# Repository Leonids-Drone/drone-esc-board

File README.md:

# Electric speed control board

Single channel ESC designed for Leonids drone, compatible with AM32 firmware.

## Current stage: Demo board

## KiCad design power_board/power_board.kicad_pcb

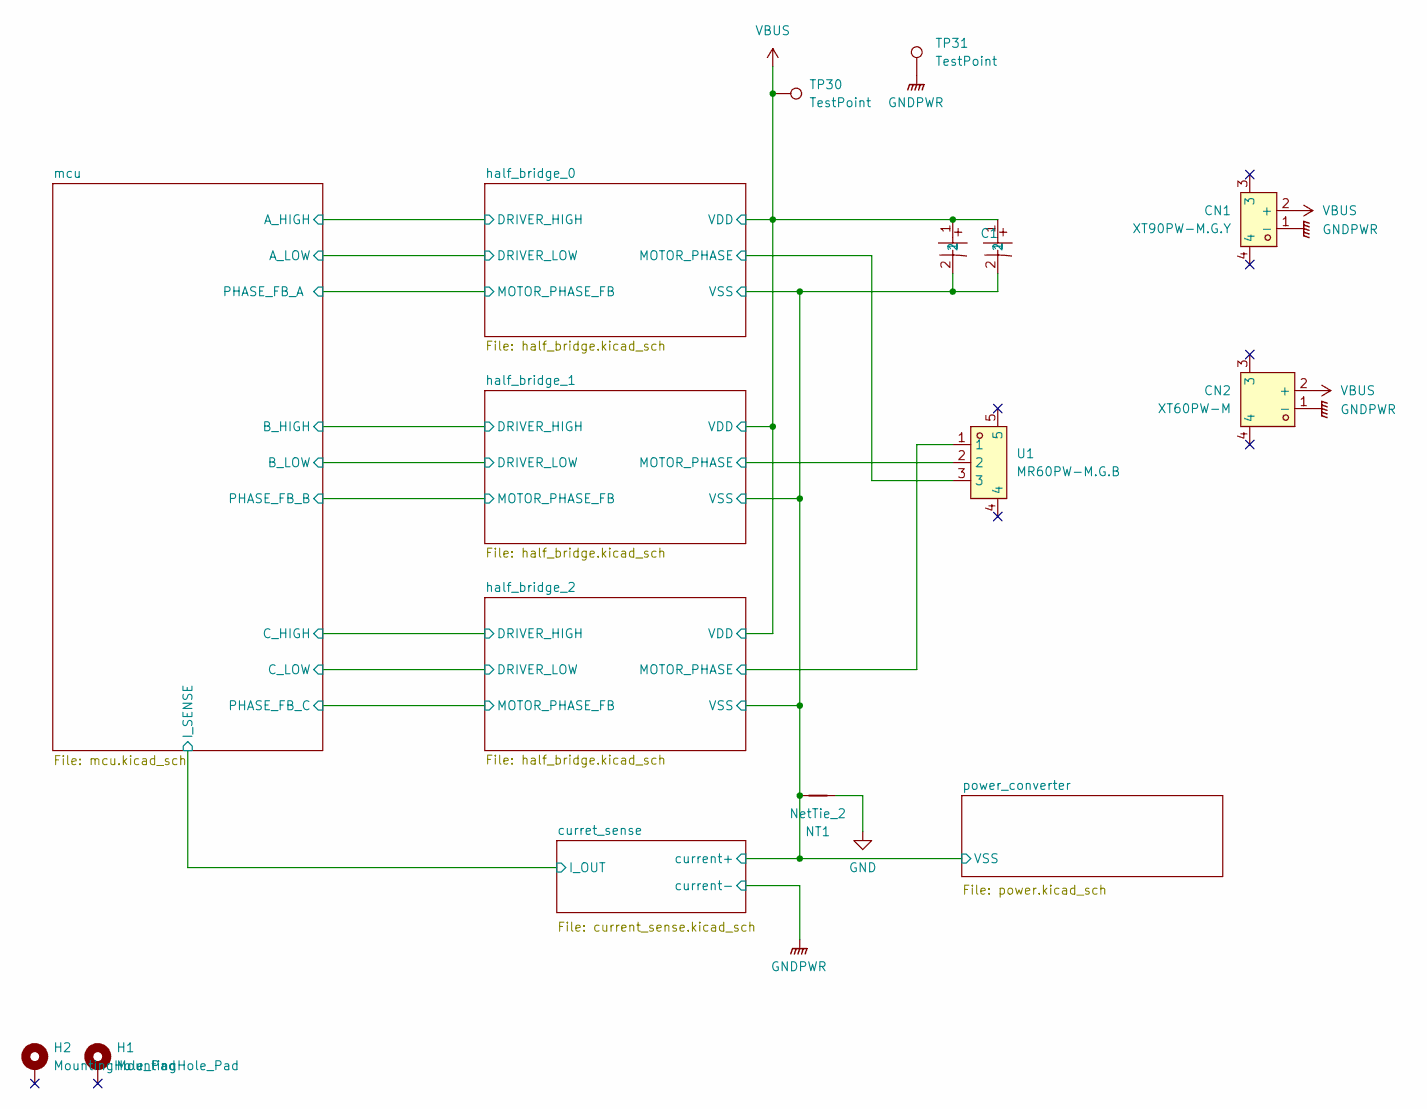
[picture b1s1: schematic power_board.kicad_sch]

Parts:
C1, C2: ERS1KM101G16OT; CAP-TH_BD10.0-P5.00-D1.0-FD; LCSC Part C106679
CN1: XT90PW-M.G.Y; CONN-TH_XT90PW-M.G.Y; LCSC Part C3040689
CN2: XT60PW-M; CONN-TH_XT60PW-M; LCSC Part C98732
H1, H2: MountingHole_Pad; MountingHole_4.3mm_M4_Pad_Via
NT1: NetTie_2; NetTie-2_THT_Pad0.3mm
TP30, TP31: TestPoint; SMD_RH-5015
U1: MR60PW-M.G.B; CONN-TH_MR60PW; LCSC Part C19268044

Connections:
/curret_sense/current+: C1.2, C2.2, NT1.2; also elsewhere on the board
/half_bridge_0/MOTOR_PHASE: U1.3; also elsewhere on the board
/half_bridge_1/MOTOR_PHASE: U1.2; also elsewhere on the board
/half_bridge_2/MOTOR_PHASE: U1.1; also elsewhere on the board
GND: NT1.1; also elsewhere on the board
GNDPWR: CN1.1 (-), CN2.1 (-), TP31.1; also elsewhere on the board
VBUS: C1.1, C2.1, CN1.2 (+), CN2.2 (+), TP30.1; also elsewhere on the board

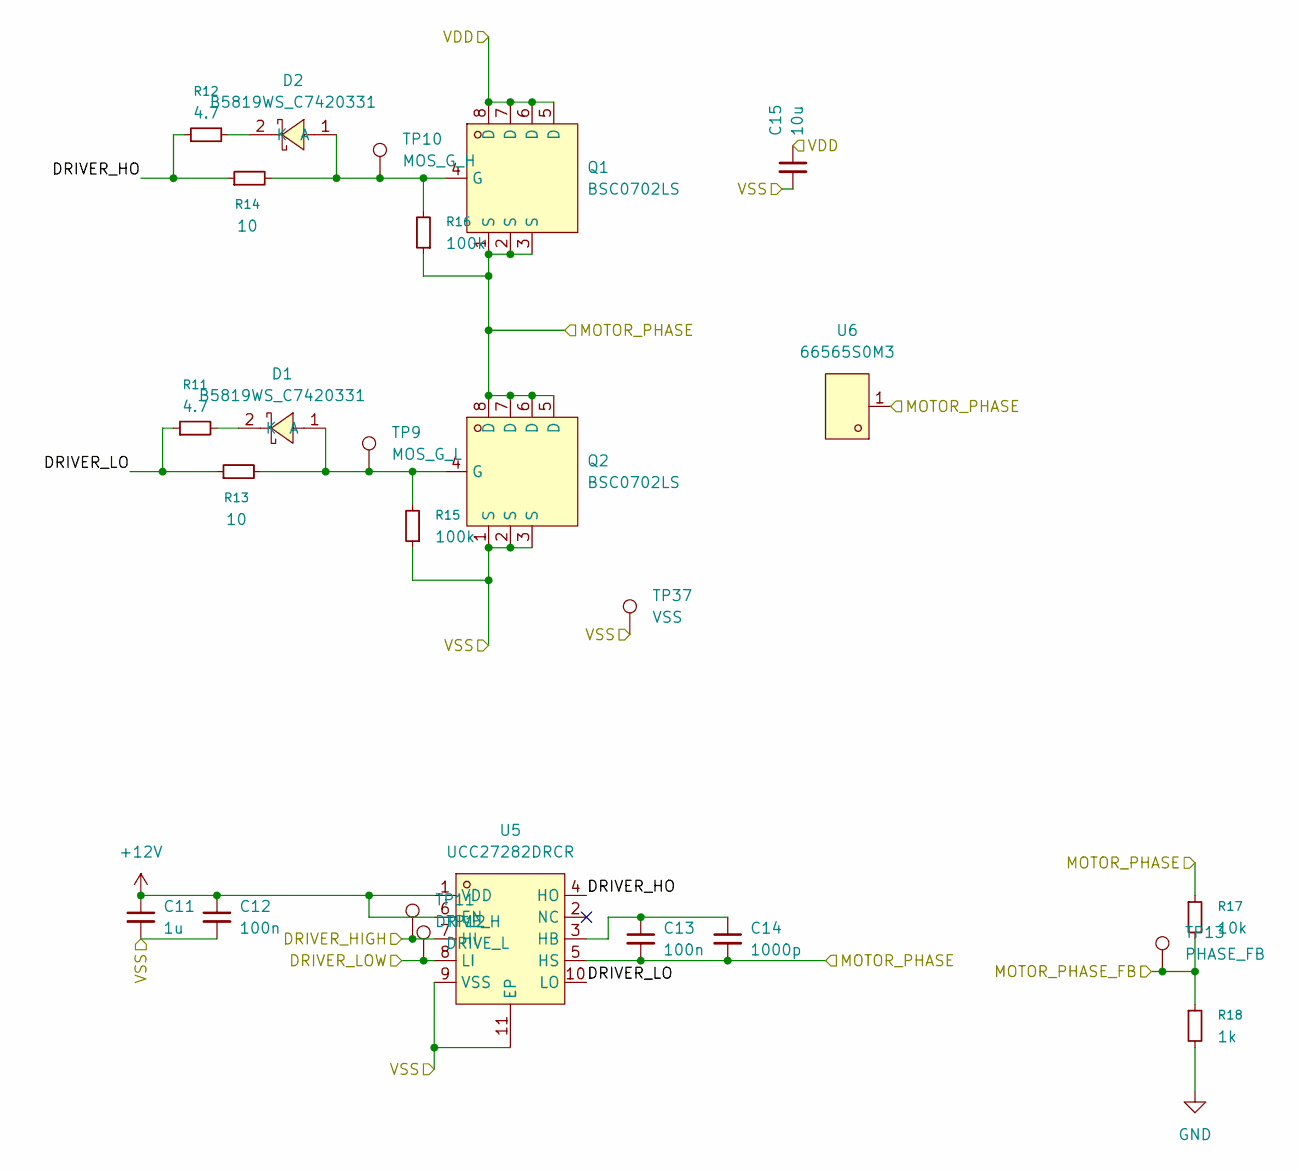
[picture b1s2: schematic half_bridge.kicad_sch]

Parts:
C11: 1u; C_0603_1608Metric
C12, C13: 100n; C_0603_1608Metric
C14: 1000p; C_0603_1608Metric
C15: 10u; C_1210_3225Metric
D1, D2: B5819WS_C7420331; SOD-323_L1.7-W1.3-LS2.5-FD; LCSC Part C7420331
Q1, Q2: BSC0702LS; PG-TDSON-8_L5.0-W6.0-P1.27-BL-EP; LCSC Part C501503
R11, R12: 4.7; R_0603_1608Metric
R13, R14: 10; R_0603_1608Metric
R15, R16: 100k; R_0603_1608Metric
R17: 10k; R_0603_1608Metric
R18: 1k; R_0603_1608Metric
TP9: MOS_G_L; SMD_RH-5015
TP10: MOS_G_H; SMD_RH-5015
TP11: DRIVE_H; SMD_RH-5015
TP12: DRIVE_L; SMD_RH-5015
TP13: PHASE_FB; SMD_RH-5015
TP37: VSS; SMD_RH-5015
U5: UCC27282DRCR; VSON-10_L3.0-W3.0-P0.50-TL-EP; LCSC Part C2677035
U6: 66565S0M3; CONN-SMD_66565S0M3; LCSC Part C41416690

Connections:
+12V: C11.1, C12.1, U5.1 (VDD), U5.6 (EN); also elsewhere on the board
/curret_sense/current+: C11.2, C12.2, C15.2, Q2.1 (S), Q2.2 (S), Q2.3 (S), R15.1, TP37.1, U5.9 (VSS), U5.11 (EP); also elsewhere on the board
/half_bridge_0/DRIVER_HIGH: TP11.1, U5.7 (HI); also elsewhere on the board
/half_bridge_0/DRIVER_HO: R12.1, R14.1, U5.4 (HO)
/half_bridge_0/DRIVER_LO: R11.1, R13.1, U5.10 (LO)
/half_bridge_0/DRIVER_LOW: TP12.1, U5.8 (LI); also elsewhere on the board
/half_bridge_0/MOTOR_PHASE: C13.2, C14.2, Q1.1 (S), Q1.2 (S), Q1.3 (S), Q2.5 (D), Q2.6 (D), Q2.7 (D), Q2.8 (D), R16.1, R17.1, U5.5 (HS), U6.1; also elsewhere on the board
/half_bridge_0/MOTOR_PHASE_FB: R17.2, R18.1, TP13.1; also elsewhere on the board
GND: R18.2; also elsewhere on the board
unnamed: D1.1 (A), Q2.4 (G), R13.2, R15.2, TP9.1
unnamed: D1.2 (K), R11.2
unnamed: D2.1 (A), Q1.4 (G), R14.2, R16.2, TP10.1
unnamed: D2.2 (K), R12.2
unnamed: C13.1, C14.1, U5.3 (HB)
VBUS: C15.1, Q1.5 (D), Q1.6 (D), Q1.7 (D), Q1.8 (D); also elsewhere on the board

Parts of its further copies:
C16, C21: 1u; C_0603_1608Metric
C17, C18, C22, C23: 100n; C_0603_1608Metric
C19, C24: 1000p; C_0603_1608Metric
C20, C25: 10u; C_1210_3225Metric
D3, D4, D5, D6: B5819WS_C7420331; SOD-323_L1.7-W1.3-LS2.5-FD; LCSC Part C7420331
Q3, Q4, Q5, Q6: BSC0702LS; PG-TDSON-8_L5.0-W6.0-P1.27-BL-EP; LCSC Part C501503
R19, R20, R27, R28: 4.7; R_0603_1608Metric
R21, R22, R29, R30: 10; R_0603_1608Metric
R23, R24, R31, R32: 100k; R_0603_1608Metric
R25, R33: 10k; R_0603_1608Metric
R26, R34: 1k; R_0603_1608Metric
TP14, TP19: MOS_G_L; SMD_RH-5015
TP15, TP20: MOS_G_H; SMD_RH-5015
TP16, TP21: DRIVE_H; SMD_RH-5015
TP17, TP22: DRIVE_L; SMD_RH-5015
TP18, TP23: PHASE_FB; SMD_RH-5015
TP38, TP39: VSS; SMD_RH-5015
U7, U9: UCC27282DRCR; VSON-10_L3.0-W3.0-P0.50-TL-EP; LCSC Part C2677035
U8, U10: 66565S0M3; CONN-SMD_66565S0M3; LCSC Part C41416690

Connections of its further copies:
+12V: C16.1, C17.1, C21.1, C22.1, U7.1 (VDD), U7.6 (EN), U9.1 (VDD), U9.6 (EN); also elsewhere on the board
/curret_sense/current+: C16.2, C17.2, C20.2, C21.2, C22.2, C25.2, Q4.1 (S), Q4.2 (S), Q4.3 (S), Q6.1 (S), Q6.2 (S), Q6.3 (S), R23.1, R31.1, TP38.1, TP39.1, U7.9 (VSS), U7.11 (EP), U9.9 (VSS), U9.11 (EP); also elsewhere on the board
/half_bridge_1/DRIVER_HIGH: TP16.1, U7.7 (HI); also elsewhere on the board
/half_bridge_1/DRIVER_HO: R20.1, R22.1, U7.4 (HO)
/half_bridge_1/DRIVER_LO: R19.1, R21.1, U7.10 (LO)
/half_bridge_1/DRIVER_LOW: TP17.1, U7.8 (LI); also elsewhere on the board
/half_bridge_1/MOTOR_PHASE: C18.2, C19.2, Q3.1 (S), Q3.2 (S), Q3.3 (S), Q4.5 (D), Q4.6 (D), Q4.7 (D), Q4.8 (D), R24.1, R25.1, U7.5 (HS), U8.1; also elsewhere on the board
/half_bridge_1/MOTOR_PHASE_FB: R25.2, R26.1, TP18.1; also elsewhere on the board
/half_bridge_2/DRIVER_HIGH: TP21.1, U9.7 (HI); also elsewhere on the board
/half_bridge_2/DRIVER_HO: R28.1, R30.1, U9.4 (HO)
/half_bridge_2/DRIVER_LO: R27.1, R29.1, U9.10 (LO)
/half_bridge_2/DRIVER_LOW: TP22.1, U9.8 (LI); also elsewhere on the board
/half_bridge_2/MOTOR_PHASE: C23.2, C24.2, Q5.1 (S), Q5.2 (S), Q5.3 (S), Q6.5 (D), Q6.6 (D), Q6.7 (D), Q6.8 (D), R32.1, R33.1, U9.5 (HS), U10.1; also elsewhere on the board
/half_bridge_2/MOTOR_PHASE_FB: R33.2, R34.1, TP23.1; also elsewhere on the board
GND: R26.2, R34.2; also elsewhere on the board
unnamed: D3.1 (A), Q4.4 (G), R21.2, R23.2, TP14.1
unnamed: D3.2 (K), R19.2
unnamed: D4.1 (A), Q3.4 (G), R22.2, R24.2, TP15.1
unnamed: D4.2 (K), R20.2
unnamed: D5.1 (A), Q6.4 (G), R29.2, R31.2, TP19.1
unnamed: D5.2 (K), R27.2
unnamed: D6.1 (A), Q5.4 (G), R30.2, R32.2, TP20.1
unnamed: D6.2 (K), R28.2
unnamed: C18.1, C19.1, U7.3 (HB)
unnamed: C23.1, C24.1, U9.3 (HB)
VBUS: C20.1, C25.1, Q3.5 (D), Q3.6 (D), Q3.7 (D), Q3.8 (D), Q5.5 (D), Q5.6 (D), Q5.7 (D), Q5.8 (D); also elsewhere on the board

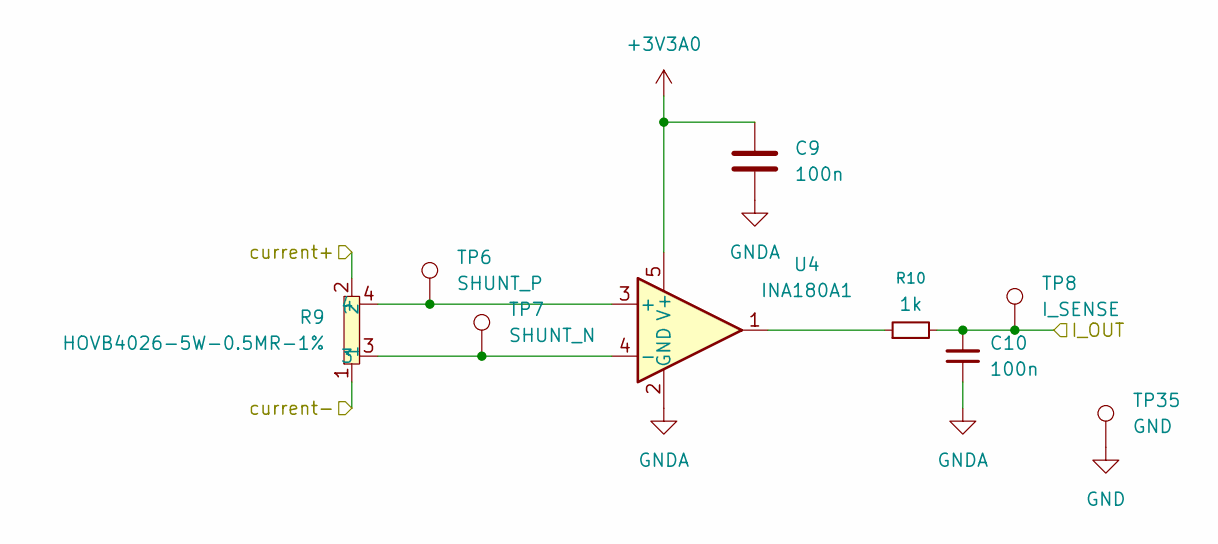
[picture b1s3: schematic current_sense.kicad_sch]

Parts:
C9, C10: 100n; C_0603_1608Metric
R9: HOVB4026-5W-0.5MR-1%; RES-SMD_4P-L10.8-W6.7; LCSC Part C481533
R10: 1k; R_0603_1608Metric
TP6: SHUNT_P; SMD_RH-5015
TP7: SHUNT_N; SMD_RH-5015
TP8: I_SENSE; SMD_RH-5015
TP35: GND; SMD_RH-5015
U4: INA180A1; SOT-23-5

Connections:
+3V3A0: C9.1, U4.5 (V+); also elsewhere on the board
/curret_sense/I_OUT: C10.2, R10.2, TP8.1; also elsewhere on the board
/curret_sense/current+: R9.2; also elsewhere on the board
GND: C9.2, C10.1, TP35.1, U4.2 (GND); also elsewhere on the board
GNDPWR: R9.1; also elsewhere on the board
unnamed: R10.1, U4.1
unnamed: R9.4, TP6.1, U4.3 (+)
unnamed: R9.3, TP7.1, U4.4 (-)

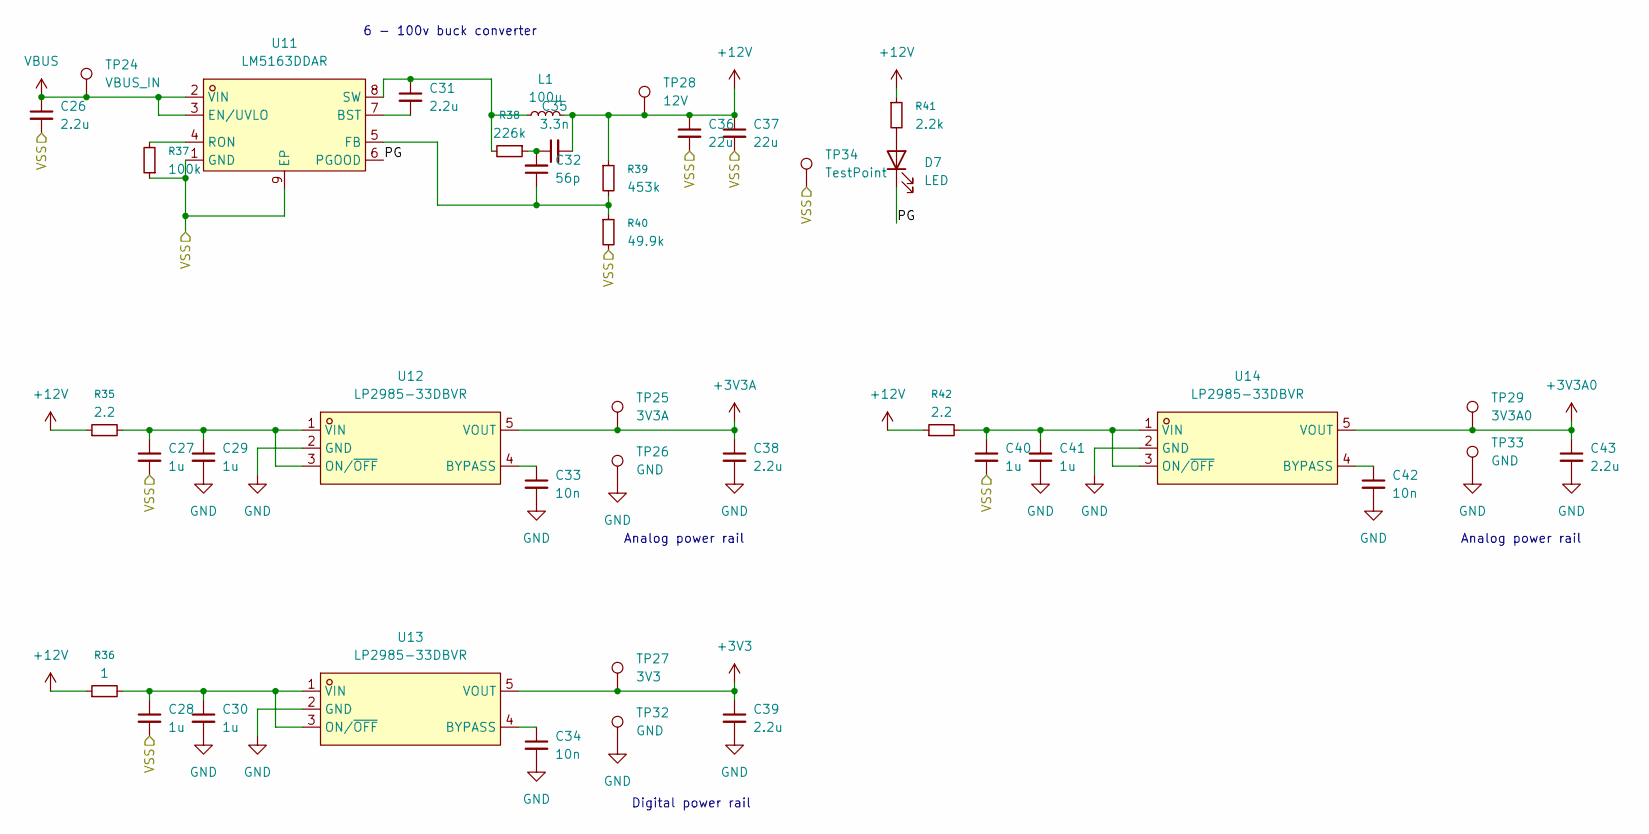
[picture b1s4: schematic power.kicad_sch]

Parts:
C26, C31, C38, C39, C43: 2.2u; C_0603_1608Metric
C27, C28, C29, C30, C40, C41: 1u; C_0603_1608Metric
C32: 56p; C_0603_1608Metric
C33, C34, C42: 10n; C_0603_1608Metric
C35: 3.3n; C_0603_1608Metric
C36, C37: 22u; C_1210_3225Metric
D7: LED; LED_0603_1608Metric
L1: 100u; L_7.3x7.3_H4.5
R35, R42: 2.2; R_0603_1608Metric
R36: 1; R_0603_1608Metric
R37: 100k; R_0603_1608Metric
R38: 226k; R_0603_1608Metric
R39: 453k; R_0603_1608Metric
R40: 49.9k; R_0603_1608Metric
R41: 2.2k; R_0603_1608Metric
TP24: VBUS_IN; SMD_RH-5015
TP25: 3V3A; SMD_RH-5015
TP26, TP32, TP33: GND; SMD_RH-5015
TP27: 3V3; SMD_RH-5015
TP28: 12V; SMD_RH-5015
TP29: 3V3A0; SMD_RH-5015
TP34: TestPoint; SMD_RH-5015
U11: LM5163DDAR; ESOP-8_L4.9-W3.9-P1.27-LS6.0-BL-EP2.6; LCSC Part C2873264
U12, U13, U14: LP2985-33DBVR; SOT-23-5_L3.0-W1.7-P0.95-LS2.8-BR; LCSC Part C95414

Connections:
+3V3: C39.1, TP27.1, U13.5 (VOUT); also elsewhere on the board
+3V3A: C38.1, TP25.1, U12.5 (VOUT); also elsewhere on the board
+3V3A0: C43.1, TP29.1, U14.5 (VOUT); also elsewhere on the board
+12V: C35.2, C36.1, C37.1, L1.2, R35.1, R36.1, R39.1, R41.1, R42.1, TP28.1; also elsewhere on the board
/curret_sense/current+: C26.2, C27.2, C28.2, C36.2, C37.2, C40.2, R37.1, R40.2, TP34.1, U11.1 (GND), U11.9 (EP); also elsewhere on the board
/power_converter/PG: D7.1 (K), U11.6 (PGOOD)
GND: C29.2, C30.2, C33.2, C34.2, C38.2, C39.2, C41.2, C42.2, C43.2, TP26.1, TP32.1, TP33.1, U12.2 (GND), U13.2 (GND), U14.2 (GND); also elsewhere on the board
unnamed: C32.2, C35.1, R38.1
unnamed: D7.2 (A), R41.2
unnamed: C31.2, U11.7 (BST)
unnamed: C32.1, R39.2, R40.1, U11.5 (FB)
unnamed: R37.2, U11.4 (RON)
unnamed: C31.1, L1.1, R38.2, U11.8 (SW)
unnamed: C33.1, U12.4 (BYPASS)
unnamed: C27.1, C29.1, R35.2, U12.1 (VIN), U12.3 (ON/~OFF)
unnamed: C34.1, U13.4 (BYPASS)
unnamed: C28.1, C30.1, R36.2, U13.1 (VIN), U13.3 (ON/~OFF)
unnamed: C42.1, U14.4 (BYPASS)
unnamed: C40.1, C41.1, R42.2, U14.1 (VIN), U14.3 (ON/~OFF)
VBUS: C26.1, TP24.1, U11.2 (VIN), U11.3 (EN/UVLO); also elsewhere on the board

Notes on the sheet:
Analog power rail
Digital power rail
6 - 100v buck converter

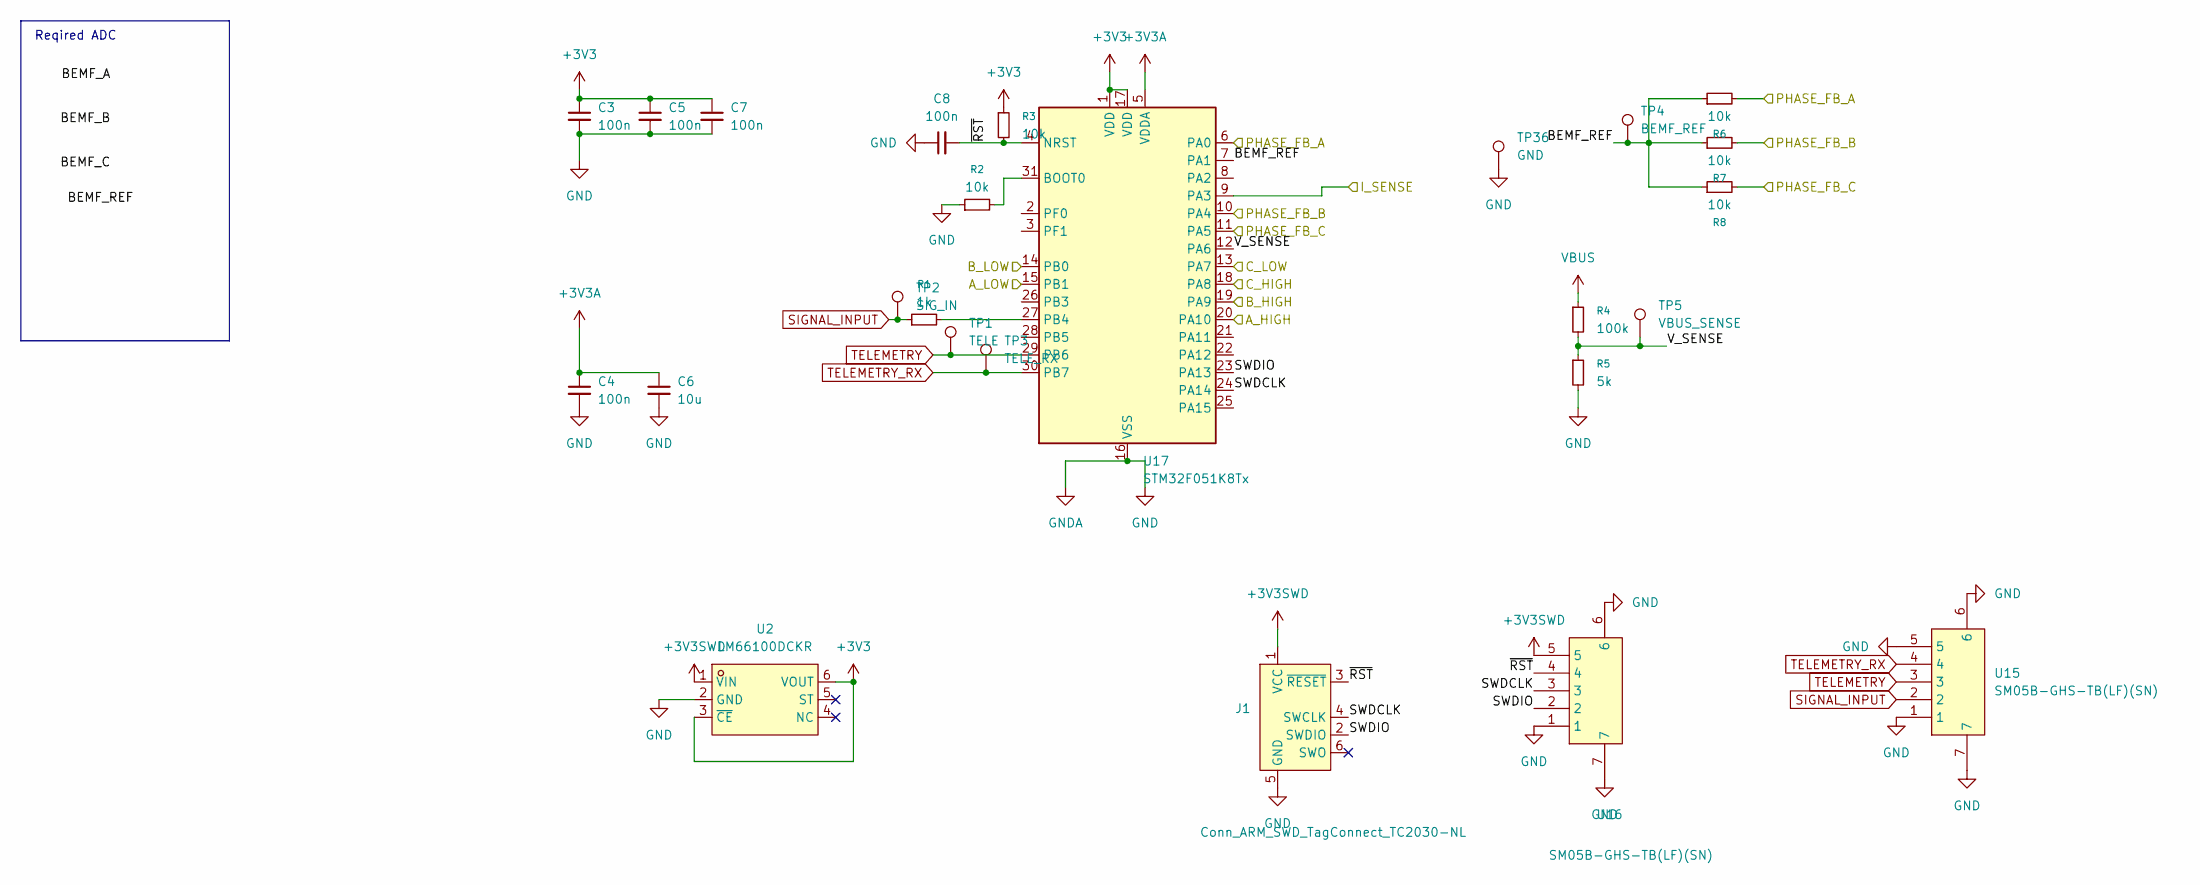
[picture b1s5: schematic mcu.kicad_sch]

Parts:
C3, C4, C5, C7, C8: 100n; C_0603_1608Metric
C6: 10u; C_0603_1608Metric
J1: Conn_ARM_SWD_TagConnect_TC2030-NL; Tag-Connect_TC2030-IDC-NL_2x03_P1.27mm_Vertical
R1: 1k; R_0603_1608Metric
R2, R3, R6, R7, R8: 10k; R_0603_1608Metric
R4: 100k; R_0603_1608Metric
R5: 5k; R_0603_1608Metric
TP1: TELE; SMD_RH-5015
TP2: SIG_IN; SMD_RH-5015
TP3: TELE_RX; SMD_RH-5015
TP4: BEMF_REF; SMD_RH-5015
TP5: VBUS_SENSE; SMD_RH-5015
TP36: GND; SMD_RH-5015
U2: LM66100DCKR; SC-70-6_L2.0-W1.3-P0.65-LS2.1-BL; LCSC Part C2869734
U15, U16: SM05B-GHS-TB(LF)(SN); CONN-SMD_5P-P1.25_SM05B-GHS-TB-LF-SN; LCSC Part C189896
U17: STM32F051K8Tx; UFQFPN-32-1EP_5x5mm_P0.5mm_EP3.5x3.5mm

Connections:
+3V3: C3.1, C5.1, C7.1, R3.1, U2.3 (~CE), U2.6 (VOUT), U17.1 (VDD), U17.17 (VDD); also elsewhere on the board
+3V3A: C4.1, C6.1, U17.5 (VDDA); also elsewhere on the board
+3V3SWD: J1.1 (VCC), U2.1 (VIN), U16.5
/curret_sense/I_OUT: U17.9 (PA3); also elsewhere on the board
/half_bridge_0/DRIVER_HIGH: U17.20 (PA10); also elsewhere on the board
/half_bridge_0/DRIVER_LOW: U17.15 (PB1); also elsewhere on the board
/half_bridge_0/MOTOR_PHASE_FB: R6.2, U17.6 (PA0); also elsewhere on the board
/half_bridge_1/DRIVER_HIGH: U17.19 (PA9); also elsewhere on the board
/half_bridge_1/DRIVER_LOW: U17.14 (PB0); also elsewhere on the board
/half_bridge_1/MOTOR_PHASE_FB: R7.2, U17.10 (PA4); also elsewhere on the board
/half_bridge_2/DRIVER_HIGH: U17.18 (PA8); also elsewhere on the board
/half_bridge_2/DRIVER_LOW: U17.13 (PA7); also elsewhere on the board
/half_bridge_2/MOTOR_PHASE_FB: R8.2, U17.11 (PA5); also elsewhere on the board
/mcu/BEMF_REF: R6.1, R7.1, R8.1, TP4.1, U17.7 (PA1)
/mcu/SWDCLK: J1.4 (SWCLK), U16.3, U17.24 (PA14)
/mcu/SWDIO: J1.2 (SWDIO), U16.2, U17.23 (PA13)
/mcu/V_SENSE: R4.2, R5.1, TP5.1, U17.12 (PA6)
/mcu/~RST: C8.2, J1.3 (~RESET), R3.2, U16.4, U17.4 (NRST)
GND: C3.2, C4.2, C5.2, C6.2, C7.2, C8.1, J1.5 (GND), R2.1, R5.2, TP36.1, U2.2 (GND), U15.1, U15.5, U15.6, U15.7, U16.1, U16.6, U16.7, U17.16 (VSS), U17.32 (VSS), U17.33; also elsewhere on the board
unnamed: R2.2, U17.31 (BOOT0)
unnamed: R1.2, U17.27 (PB4)
SIGNAL_INPUT: R1.1, TP2.1, U15.2
TELEMETRY: TP1.1, U15.3, U17.29 (PB6)
TELEMETRY_RX: TP3.1, U15.4, U17.30 (PB7)
VBUS: R4.1; also elsewhere on the board

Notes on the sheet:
Reqired ADC

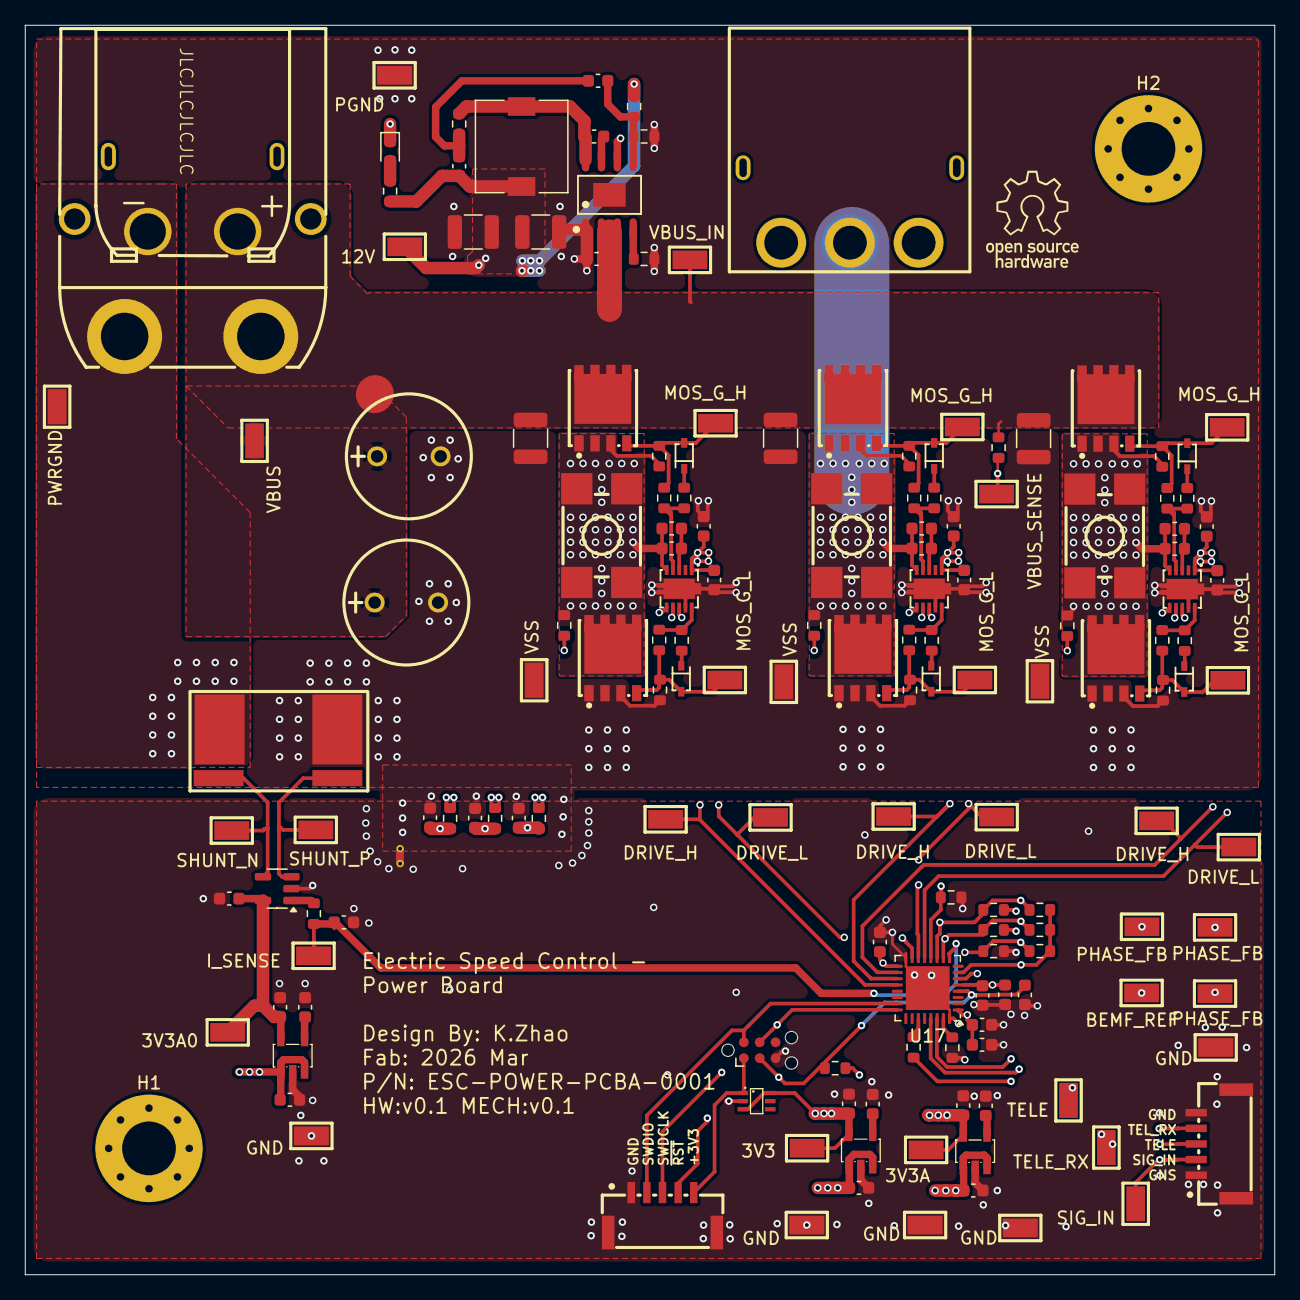
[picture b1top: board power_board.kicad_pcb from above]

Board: 4 copper layers, 100.0 x 100.0 mm, 160 parts (0 on the bottom side), 69 nets.

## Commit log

2026-01-12 Complete mosfet design per channel
2026-03-12 Seperat submodules into split sheets
2026-03-12 Complete sch design without check
2026-03-14 Start multichannel layout
2026-03-14 Complete primary layout step
2026-03-15 Phase control signal layout
2026-03-16 Complete layout, and copper zone design
    TODO!!!: move DCDC zone from GND area to PGND(current+)
2026-03-16 All drc error solved
2026-03-17 Add testpoint, SWD, and PWM port
2026-03-19 Complete all design, pass DRC
2026-03-20 change mcu to STM32F051K8U6
2026-03-20 Add JLCJLCJLCJLC
2026-03-20 Move to Kicad 10
